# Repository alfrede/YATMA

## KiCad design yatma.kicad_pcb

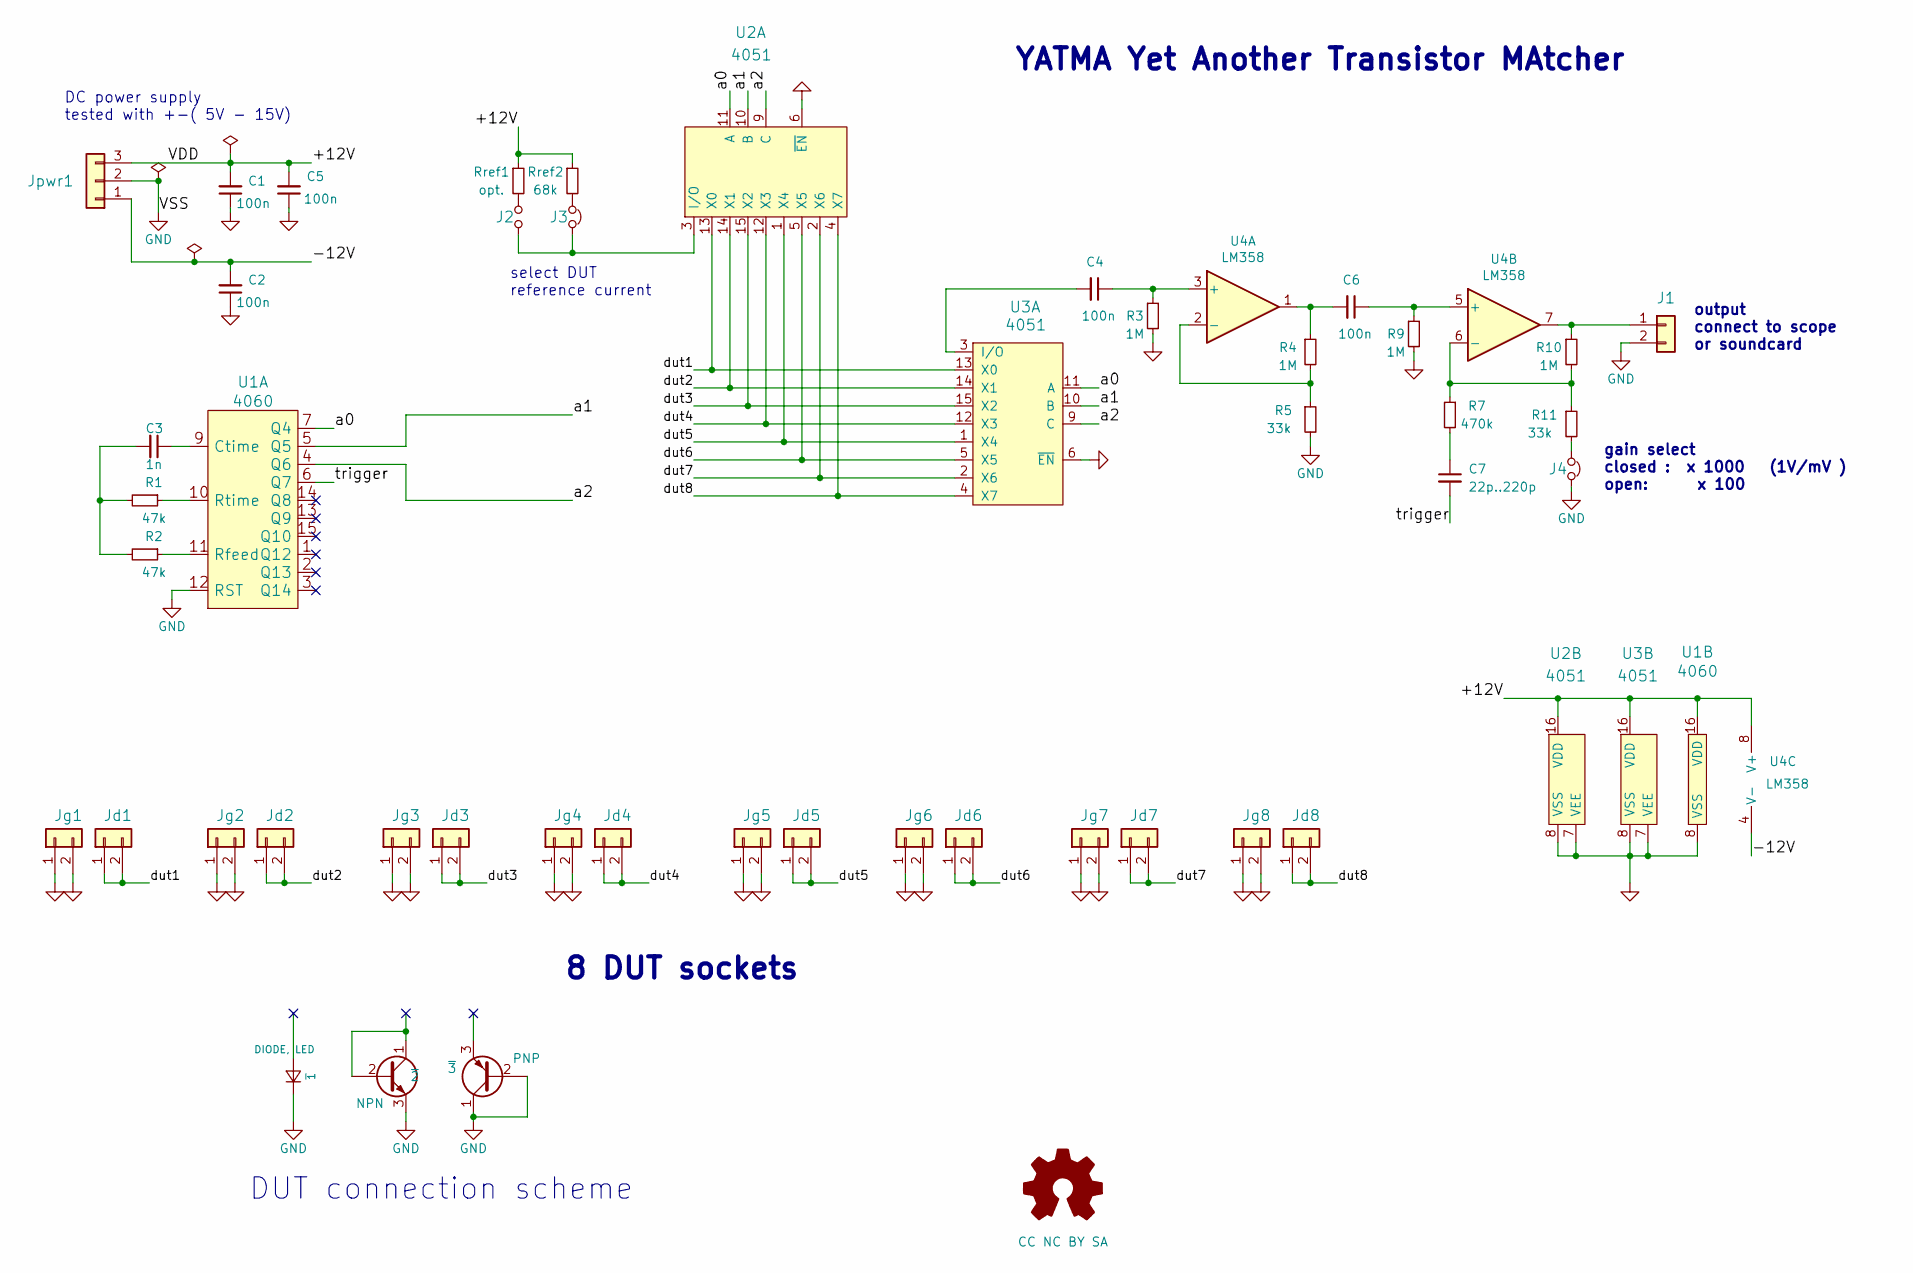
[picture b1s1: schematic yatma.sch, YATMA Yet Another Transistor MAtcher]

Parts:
C1, C2, C4, C5, C6: 100n; C_Rect_L7.0mm_W2.0mm_P5.00mm
C3: 1n; C_Rect_L7.0mm_W2.0mm_P5.00mm
C7: 22p..220p; C_Disc_D6.0mm_W2.5mm_P5.00mm
J1: HEADER_2; BNC_Amphenol_B6252HB-NPP3G-50_Horizontal
J2: opt; PinHeader_1x02_P2.54mm_Vertical
J3: Iref; PinHeader_1x02_P2.54mm_Vertical
J4: gain; PinHeader_1x02_P2.54mm_Vertical
Jd1, Jd2, Jd3, Jd4, Jd5, Jd6, Jd7, Jd8: dut; PinSocket_1x02_P2.54mm_Vertical
Jg1, Jg2, Jg3, Jg4, Jg5, Jg6, Jg7, Jg8: dut; PinSocket_1x02_P2.54mm_Vertical
Jpwr1: +0-; PinHeader_1x03_P2.54mm_Vertical
R1, R2: 47k; R_Axial_DIN0207_L6.3mm_D2.5mm_P10.16mm_Horizontal
R3, R4, R9, R10: 1M; R_Axial_DIN0207_L6.3mm_D2.5mm_P10.16mm_Horizontal
R5, R11: 33k; R_Axial_DIN0207_L6.3mm_D2.5mm_P10.16mm_Horizontal
R7: 470k; R_Axial_DIN0207_L6.3mm_D2.5mm_P10.16mm_Horizontal
Rref1: opt.; R_Axial_DIN0207_L6.3mm_D2.5mm_P10.16mm_Horizontal
Rref2: 68k; R_Axial_DIN0207_L6.3mm_D2.5mm_P10.16mm_Horizontal
U1: 4060; DIP-16_W7.62mm_LongPads
U2, U3: 4051; DIP-16_W7.62mm_LongPads
U4: LM358; DIP-8_W7.62mm_LongPads
~1: DIODE, LED
~2: NPN
~3: PNP

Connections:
/+12V: C1.2, C5.2, Jpwr1.3, Rref1.1, Rref2.1, U1.16 (VDD), U2.16 (VDD), U3.16 (VDD), U4.8 (V+)
/-12V: C2.2, Jpwr1.1, U4.4 (V-)
/a0: U1.7 (Q4), U2.11 (A), U3.11 (A)
/a1: U1.5 (Q5), U2.10 (B), U3.10 (B)
/a2: U1.4 (Q6), U2.9 (C), U3.9 (C)
/dut1: Jd1.1, Jd1.2, U2.13 (X0), U3.13 (X0)
/dut2: Jd2.1, Jd2.2, U2.14 (X1), U3.14 (X1)
/dut3: Jd3.1, Jd3.2, U2.15 (X2), U3.15 (X2)
/dut4: Jd4.1, Jd4.2, U2.12 (X3), U3.12 (X3)
/dut5: Jd5.1, Jd5.2, U2.1 (X4), U3.1 (X4)
/dut6: Jd6.1, Jd6.2, U2.5 (X5), U3.5 (X5)
/dut7: Jd7.1, Jd7.2, U2.2 (X6), U3.2 (X6)
/dut8: Jd8.1, Jd8.2, U2.4 (X7), U3.4 (X7)
/trigger: C7.2, U1.6 (Q7)
GND: C1.1, C2.1, C5.1, J1.2, J4.1, Jg1.1, Jg1.2, Jg2.1, Jg2.2, Jg3.1, Jg3.2, Jg4.1, Jg4.2, Jg5.1, Jg5.2, Jg6.1, Jg6.2, Jg7.1, Jg7.2, Jg8.1, Jg8.2, Jpwr1.2, R3.2, R5.2, R9.2, U1.8 (VSS), U1.12 (RST), U2.6 (~EN), U2.7 (VEE), U2.8 (VSS), U3.6 (~EN), U3.7 (VEE), U3.8 (VSS), ~1.1 (K), ~2.3 (E), ~3.1 (C), ~3.2 (B)
unnamed: C3.1, U1.9 (Ctime)
unnamed: C3.2, R1.2, R2.2
unnamed: C4.1, R3.1, U4.3 (+)
unnamed: C4.2, U3.3 (I/O)
unnamed: C6.1, R9.1, U4.5 (+)
unnamed: C6.2, R4.1, U4.1
unnamed: C7.1, R7.2
unnamed: J1.1, R10.1, U4.7
unnamed: J2.1, J3.1, U2.3 (I/O)
unnamed: J2.2, Rref1.2
unnamed: J3.2, Rref2.2
unnamed: J4.2, R11.2
unnamed: R1.1, U1.10 (Rtime)
unnamed: R2.1, U1.11 (Rfeed)
unnamed: R4.2, R5.1, U4.2 (-)
unnamed: R7.1, R10.2, R11.1, U4.6 (-)
unnamed: ~2.1 (C), ~2.2 (B)

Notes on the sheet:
DC power supply tested with +-( 5V - 15V)
DUT connection scheme
select DUT reference current
8 DUT sockets
YATMA Yet Another Transistor MAtcher
gain select closed : x 1000 (1V/mV ) open: x 100
output connect to scope or soundcard

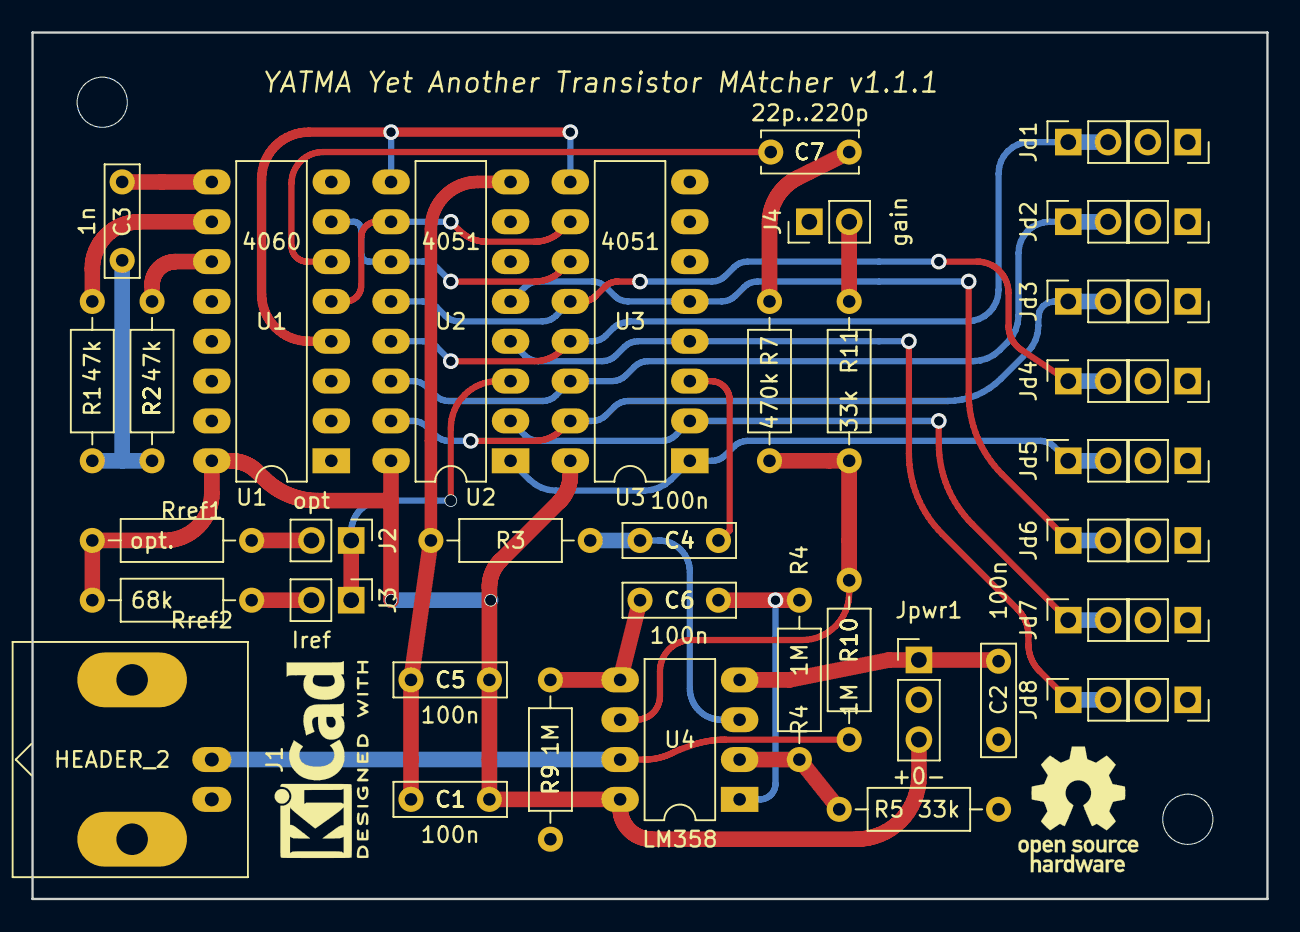
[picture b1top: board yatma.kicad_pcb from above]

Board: 2 copper layers, 78.7 x 55.2 mm, 43 parts (0 on the bottom side), 31 nets.

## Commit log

2021-05-21 Inital Commit
    Add Files with Changes from me.
2021-05-21 Revert "Inital Commit"
2021-05-21 Create test
2021-05-21 Add Files
    Add Files for testing
